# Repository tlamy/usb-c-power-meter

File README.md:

USB-C Power Meter Firmware

# Sources

The source code is single file and straightforward as it's only one file, main.cpp.

My current development environment is CLion using PlatformIO. As this is not easily replicable (there is no free CLion
version), I also provide premade binaries.

# Binaries

In /firmware_bin, you can find a number of premade, you guessed it, binaries.
They are named from this pattern:

**firmware_\<version\>_\<resistance\>.bin**

<a href="firmware_bin/firmware_v1.1.3_10mohm.bin">firmware_v1.1.3_10mohm.bin</a> is the first github released binary, as
I sent out a couple of meters having the wrong shunt resistor soldered on, effectively maxing out the current sensor at
around 1.6A. This version is to be used with a replacement shunt resistor of .01Ω, or 10mΩ.

## Uploading firmware

If you're unable to build it yourself, you should
follow <a href="https://github.com/SequoiaSan/Guide-How-To-Upload-bin-to-ESP8266-ESP32">SequoiaSan's guide</a> on
Github.

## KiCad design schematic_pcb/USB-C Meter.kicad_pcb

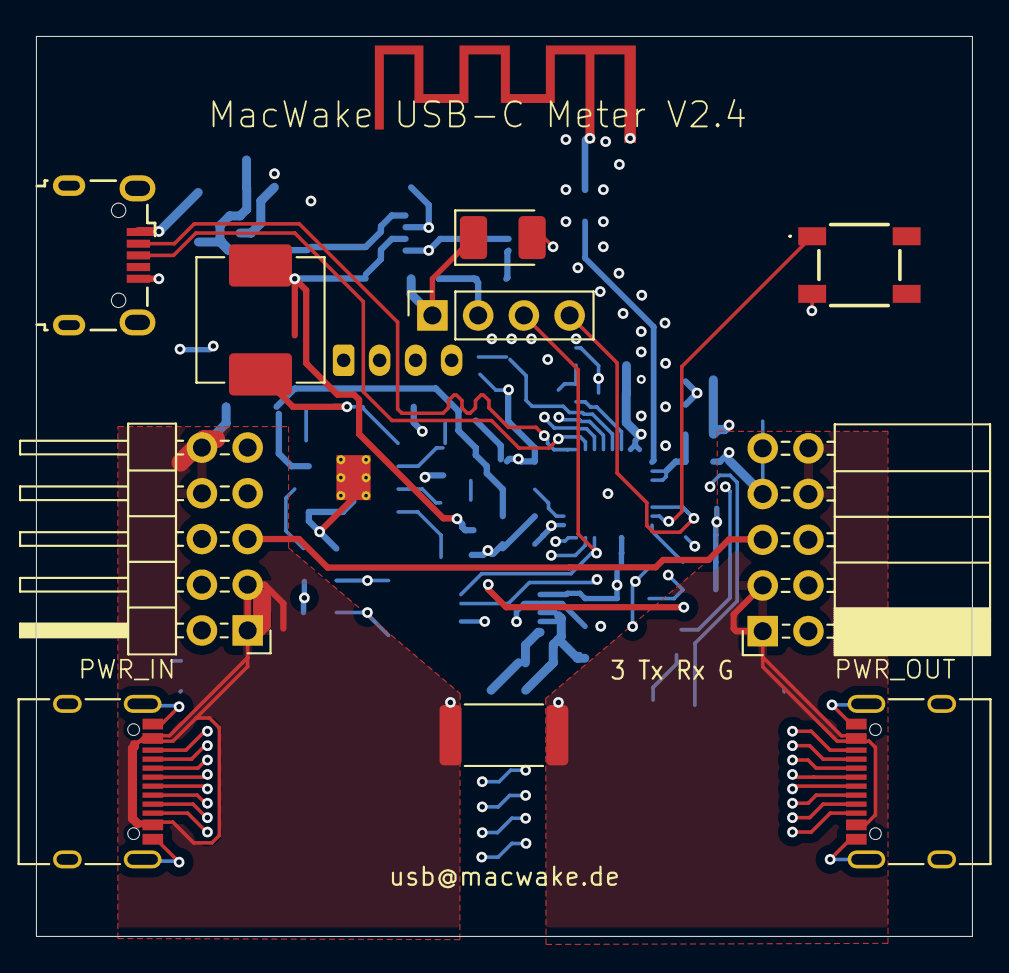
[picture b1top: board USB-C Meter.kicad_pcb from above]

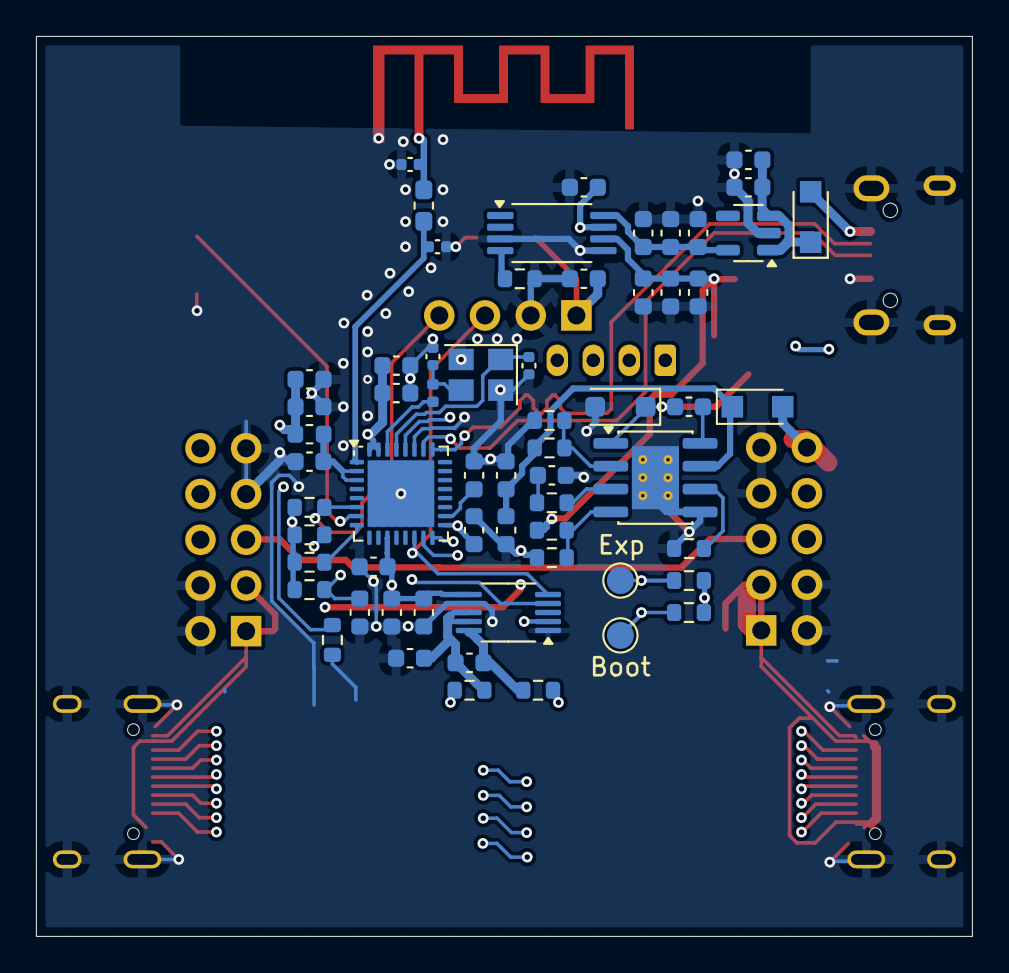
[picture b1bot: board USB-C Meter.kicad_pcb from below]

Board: 4 copper layers, 52.0 x 50.0 mm, 73 parts (61 on the bottom side), 45 nets.

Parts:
AE1: Antenna_Shield; ESPRESSIF_ESP32_MIFA_2.4GHz_Right
C1, C3, C7, C15, C16, C17, C26: 0.1µ; C_0603_1608Metric
C2, C4, C5, C6, C9, C10: 10µ; C_0603_1608Metric
C8: 2.2n; C_0603_1608Metric
C11: 22µ; C_0603_1608Metric
C12: 47µ; CP_EIA-3528-12_Kemet-T_HandSolder
C13: 10µF; C_0603_1608Metric
C14, C27, C30, C31, C32: .1µ; C_0603_1608Metric
C18, C19, C21, C29, C33: 1µ; C_0603_1608Metric
C20: 10n; C_0603_1608Metric
C22, C23: 15pF; C_0402_1005Metric
C24: 1.5p; C_0402_1005Metric
C25: 1.2p; C_0402_1005Metric
D1, D3: DS60_1; Nexperia_CFP3_SOD-123W
D2: PMEG2005EH; D_SOD-123F
J1, J2: USB-C Receptacle 16P; USB_C_Receptacle_XKB_U262-16XN-4BVC11
J3: Generic IN; PinHeader_2x05_P2.54mm_Horizontal
J4: Generic OUT; PinSocket_2x05_P2.54mm_Horizontal
J5: USB_B_Micro; USB_Micro-B_Wuerth_629105150521
J6: Display; PinSocket_1x04_P2.54mm_Vertical
J8: UART; JST_PH_B4B-PH-K_1x04_P2.00mm_Vertical
L1: 47µH; L_Changjiang_FXL0630
L2: 2.7nH; L_0603_1608Metric_Pad1.05x0.95mm_HandSolder
L3: 2nH; L_0603_1608Metric
L4: 24nH; L_0402_1005Metric
R1: 0.01R 3W; R_2512_6332Metric
R2, R3: 10R; R_0603_1608Metric
R4: 100k; R_0603_1608Metric
R5, R9: 56k; R_0603_1608Metric
R6: 200k; R_0603_1608Metric
R7: 68k; R_0603_1608Metric
R8: 22k; R_0603_1608Metric
R10: 400R; R_0603_1608Metric
R11, R12: 3k3; R_0603_1608Metric
R13: 12k; R_0603_1608Metric
R14, R15, R16: 10k; R_0603_1608Metric
R17: 500; R_0603_1608Metric
SW1: Reset; PTS647SK70SMTR2LFS
TP1: Boot; TestPoint_Pad_D1.5mm
TP2: Exp; TestPoint_Pad_D1.5mm
U1: MP4560DN; SOIC-8-1EP_3.9x4.9mm_P1.27mm_EP2.62x3.51mm_ThermalVias
U2: ME6211C33; SOT-23-5
U3: TPS2115; TSSOP-8_4.4x3mm_P0.65mm
U4: ESP32-C3FH4; QFN-32-1EP_5x5mm_P0.5mm_EP3.7x3.7mm
U6: INA228; VSSOP-10_3x3mm_P0.5mm
Y1: 40MHz; Crystal_SMD_3225-4Pin_3.2x2.5mm

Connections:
3V3: C2.1, C11.1, C12.1, C13.1, C15.1, C16.1, C17.1, C20.1, C26.1, C27.1, C33.1, J6.1, L3.1, R11.2, R12.2, R13.2, R14.2, R15.2, R16.2, U3.7 (OUT), U4.11 (VDD3P3_RTC), U4.17 (VDD3P3_CPU), U4.31 (VDDA), U4.32 (VDDA), U6.2 (A0), U6.6 (VS)
/3V3_FLT: C19.2, L3.2, U4.2 (VDD3P3), U4.3 (VDD3P3)
/ANT: AE1.1 (A), C25.1, L2.2
/BOOT: R14.1, TP1.1, U4.15 (GPIO9)
/CC1: J1.A5 (CC1), J2.B5 (CC2)
/CC2: J1.B5 (CC2), J2.A5 (CC1)
/CHGR_ID_GENERIC_A: J3.5, J4.5
/CHGR_ID_GENERIC_B: J3.6, J4.6
/D+: J5.3 (D+), U4.26 (GPIO19)
/D-: J5.2 (D-), U4.25 (GPIO18)
/EXP: R15.1, TP2.1, U4.16 (GPIO10)
/MPCOMP_RC: C8.1, R9.1
/RF: C24.2, L2.1, U4.1 (LNA_IN)
/SHNT+: C1.1, R2.2, U6.10 (Vin+)
/UTXD: R17.2, U4.28 (U0TXD)
/VBUS_DATA_3V3: C10.1, C29.1, C31.1, U2.5 (V_{OUT}), U3.8 (IN1)
/VBUS_DATA_IN: D1.2 (A), J5.1 (VBUS)
/VBUS_DATA_R: C9.1, C32.1, D1.1 (K), U2.1 (V_{IN}), U2.3 (CE)
/VBUS_PD_1_IN: D3.2 (A), J1.A4 (VBUS), J1.A9 (VBUS), J1.B4 (VBUS), J1.B9 (VBUS), J3.1, J3.3, J3.8, J3.10, R1.1, R2.1
/VBUS_PD_2_IN: J2.A4 (VBUS), J2.A9 (VBUS), J2.B4 (VBUS), J2.B9 (VBUS), J4.1, J4.3, J4.8, J4.10, R1.2, R3.2
/VBUS_PD_3V3: C5.1, C6.1, C30.1, L1.2, R7.1, U3.6 (IN2)
/VBUS_PD_R: C4.1, C14.1, D3.1 (K), R4.2, U1.7 (VIN)
GND: AE1.2 (Shield), C2.2, C3.2, C4.2, C5.2, C6.2, C8.2, C9.2, C10.2, C11.2, C12.2, C13.2, C14.2, C15.2, C16.2, C17.2, C18.1, C19.1, C20.2, C21.2, C22.1, C23.2, C24.1, C25.2, C26.2, C27.2, C29.2, C30.2, C31.2, C32.2, C33.2, D2.2 (A), J1.A1 (GND), J1.A12 (GND), J1.B1 (GND), J1.B12 (GND), J1.S1 (SHIELD), J2.A1 (GND), J2.A12 (GND), J2.B1 (GND), J2.B12 (GND), J2.S1 (SHIELD), J3.2, J3.4, J3.7, J3.9, J4.2, J4.4, J4.7, J4.9, J5.5 (GND), J5.6 (Shield), J6.2, R5.1, R6.1, R8.2, R10.2, SW1.3 (K), U1.5 (VSS), U1.9 (PAD), U2.2 (V_{SS}), U3.3 (D1), U3.5 (GND), U4.33 (GND), U6.1 (A1), U6.7 (GND), Y1.2, Y1.4
unnamed: C22.2, L4.1, Y1.3
unnamed: C7.2, D2.1 (K), L1.1, U1.1 (SW)
unnamed: J1.A6 (D+), J2.B6 (D+)
unnamed: J1.B6 (D+), J2.A6 (D+)
unnamed: J1.A7 (D-), J2.B7 (D-)
unnamed: J1.B7 (D-), J2.A7 (D-)
unnamed: J1.A8 (SBU1), J2.B8 (SBU2)
unnamed: J1.B8 (SBU2), J2.A8 (SBU1)
unnamed: C7.1, U1.8 (BST)
unnamed: R9.2, U1.3 (COMP)
unnamed: R4.1, R5.2, U1.2 (EN)
unnamed: R7.2, R8.1, U1.4 (FB)
unnamed: R6.2, U1.6 (FREQ)
unnamed: R10.1, U3.4 (ILIM)
unnamed: C21.1, R16.1, SW1.1, U4.7 (CHIP_EN)
unnamed: R13.1, U4.8 (GPIO3)
unnamed: C18.2, U4.18 (VDD_SPI)
unnamed: C23.1, U4.29 (XTAL_N), Y1.1
unnamed: L4.2, U4.30 (XTAL_P)
unnamed: C1.2, C3.1, R3.1, U6.8 (Vbus), U6.9 (Vin-)
SCL: J6.3, R12.1, U4.14 (GPIO8), U6.5 (SCL)
SDA: J6.4, R11.1, U4.6 (GPIO2), U6.4 (SDA)

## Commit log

2025-03-20 feat: First working firmware
2025-03-22 feat: first commit after switching to clion
2025-03-22 feat: copy external libraries
2025-03-22 feat: Implemented current bar
2025-04-07 Added CLion config files
2025-04-16 fix: fix configuration to match hw rev 1.1
2025-04-16 fix: remove LED debugging for max amp calculation/reset
2025-04-17 Add moving pixel when idle
2025-04-24 Added README.md and first firmware binary
2025-04-24 Added schematic and pcb (kicad)
2025-04-26 fix: explicitly mark as 10 mOhm version
2025-07-24 feat: use INA228 for hardware version 2.0
2025-08-09 feat: add Bluetooth and PowerSensor integration with BLE notifications
    Also refactored code for different components into their own classes
2025-08-13 feat: pcb/schematic v2.1.0
2025-08-16 feat: pcb/schematic v2.1.1
2025-08-17 refactor: refactored serial data communication into own class
2025-08-17 refactor: Make `Serial` dependency more explicit in SerialData class
2025-08-18 fix(pcb): fixed sda/scl pin mismatch at display connector
2025-08-18 fix: First firmware version running on esp32-c3
2025-08-23 feat(firmware): backported refactorings and display changes from v2.0
    serial current output still problematic
2025-08-23 fix(firmware): fixed shunt and voltage multipliers for PLD compatible serial output
2025-08-26 fix(firmware): added getCharge(), enhanced measurement object for BLE communication
2025-09-03 fix(firmware): Fixed INA228 current measurement to read the right register
2025-09-03 fix(firmware): removed now-unused leftovers in main.cpp
2025-09-03 fix(firmware): fixed "power" and peak current refresh rate
2025-09-06 fix(firmware): fixed voltage and power multipliers for PLD serial output
2025-09-07 fix(firmware): larger font size for "max current"
2025-09-07 style(firmware): fix some clang-tidy warnings
2025-09-16 fix: updated schematic and pcb to version 1.2
2025-09-16 release(firmware): v1.2.1 release for hardware v1.2
2025-09-17 fix(d1mini): some INAs are on 0x45 instead of the configured 0x41
2025-09-17 fix(firmware): screensaver with delay, watts display, handle negative current properly
2025-10-19 feat(firmware): suffix BLE name with part of mac address
2025-10-25 feat(hw): new buck converter enables up to 48V PD input
2026-03-05 feat: show diagnostics when EXP (GPIO10) is pulled low
2026-03-05 fix: code cleanup, better i2c diagnostics, variable display addressπ
2026-03-05 feat: added serial diagnostics (started by d[iag])
2026-03-06 feat: schematic improvements (fix some component values)
2026-03-06 fix: added zero-calibration commandπ
2026-03-09 feat: added wifi management commands and OTA setup
2026-03-12 docs: added netnames, BOM and pcb CAD export
2026-03-13 fix: show exact voltage on display, since we're no longer bound to PD levels
2026-03-14 fix: schematic/pcb v2.4 (wip)
2026-03-16 fix: rf antenna pcb design, added reset tactile switch
2026-03-23 feat: reroute antenna and all other components
2026-03-26 fix(firmware): fixed BLE device naming, reduced TX power, rate limited BLE data
